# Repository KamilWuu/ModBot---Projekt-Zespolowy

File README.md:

# ModBot---Projekt-Zespolowy

1 - Założenia projektowe
Robot modułowy ModBot będzie złożony z jednostki głównej – Platformy Mobilnej wraz z pilotem zdalnego sterowania za pomocą technologii Bluetooth. Platforma ta będzie miała możliwość
doczepienia modułów określających przeznaczenie robota:

• moduł MiniSumo,

• moduł LineFollower,

• Chwytak

2 - Cel i zakres projektu
Celem projektu jest stworzenie uniwersalnej platformy robotycznej pozwalającej na edukację
w zakresie elektroniki i programowania. Osobie uczącej się przy pomocy robota będzie da-
na możliwość samodzielnego złożenia oraz zamontowania wcześniej przygotowanych modułów,
dzięki którym robot będzie mógł wykonywać określone zadanie. Planowane są trzy domyślne
konfiguracje, za pomocą których robot będzie mógł wykonać następujące zadania:

• LineFollower – podążanie wzdłuż czarnej linii kontrastowej na białym tle, która nie posiada
zakrętów ostrzejszych niż 90◦.

• RoboSumo – przesunięcie kostki o masie zbliżonej do masy robota z standardowego ringu
Minisumo i pozostanie na ringu. Ma to na celu symulacje walki z zawodów robotycznych
z kategorii MiniSumo.

• Chwytak – utrzymanie obiektu o znacznie mniejszej masie niż jego własne poprzez moduł
zdalnego sterowania.

3 - Skład zespołu:
Kamil Winnicki - Mechanika i embedded,

Oliwier Woźniak -  Elektronika,

Patryk Peroński - Oprogramowanie i embeeded,

Rafał Koziołek - Mechanika i elektronika,

Jakub Frąckowiak - Kierownik zespołu, organizacja pracy,

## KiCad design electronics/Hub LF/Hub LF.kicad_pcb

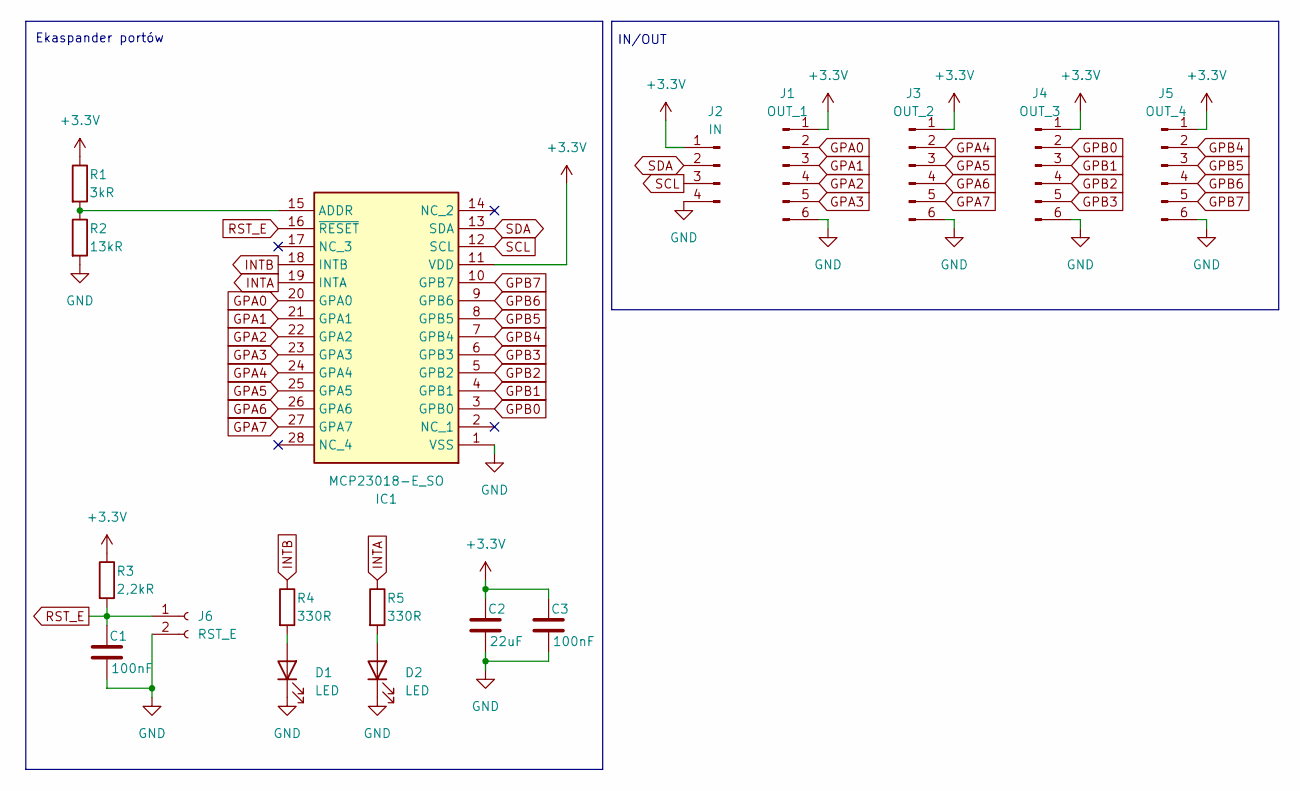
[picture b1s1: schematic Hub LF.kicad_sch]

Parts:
C1, C3: 100nF; C_0402_1005Metric_Pad0.74x0.62mm_HandSolder
C2: 22uF; C_0402_1005Metric_Pad0.74x0.62mm_HandSolder
D1, D2: LED; LED_0402_1005Metric_Pad0.77x0.64mm_HandSolder
IC1: MCP23018-E_SO; SOIC127P1030X265-28N; Manufacturer_Part_Number MCP23018-E/SO
J1: OUT_1; JST_EH_B6B-EH-A_1x06_P2.50mm_Vertical
J2: IN; JST_EH_B4B-EH-A_1x04_P2.50mm_Vertical
J3: OUT_2; JST_EH_B6B-EH-A_1x06_P2.50mm_Vertical
J4: OUT_3; JST_EH_B6B-EH-A_1x06_P2.50mm_Vertical
J5: OUT_4; JST_EH_B6B-EH-A_1x06_P2.50mm_Vertical
J6: RST_E; PinSocket_1x02_P2.54mm_Vertical
R1: 3kR; R_0402_1005Metric_Pad0.72x0.64mm_HandSolder
R2: 13kR; R_0402_1005Metric_Pad0.72x0.64mm_HandSolder
R3: 2,2kR; R_0402_1005Metric_Pad0.72x0.64mm_HandSolder
R4, R5: 330R; R_0402_1005Metric_Pad0.72x0.64mm_HandSolder

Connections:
+3.3V: C2.1, C3.1, IC1.11 (VDD), J1.1, J2.1, J3.1, J4.1, J5.1, R1.1, R3.1
GND: C1.2, C2.2, C3.2, D1.1 (K), D2.1 (K), IC1.1 (VSS), J1.6, J2.4, J3.6, J4.6, J5.6, J6.2, R2.2
GPA0: IC1.20 (GPA0), J1.2
GPA1: IC1.21 (GPA1), J1.3
GPA2: IC1.22 (GPA2), J1.4
GPA3: IC1.23 (GPA3), J1.5
GPA4: IC1.24 (GPA4), J3.2
GPA5: IC1.25 (GPA5), J3.3
GPA6: IC1.26 (GPA6), J3.4
GPA7: IC1.27 (GPA7), J3.5
GPB0: IC1.3 (GPB0), J4.2
GPB1: IC1.4 (GPB1), J4.3
GPB2: IC1.5 (GPB2), J4.4
GPB3: IC1.6 (GPB3), J4.5
GPB4: IC1.7 (GPB4), J5.2
GPB5: IC1.8 (GPB5), J5.3
GPB6: IC1.9 (GPB6), J5.4
GPB7: IC1.10 (GPB7), J5.5
INTA: IC1.19 (INTA), R5.1
INTB: IC1.18 (INTB), R4.1
unnamed: D1.2 (A), R4.2
unnamed: D2.2 (A), R5.2
unnamed: IC1.15 (ADDR), R1.2, R2.1
RST_E: C1.1, IC1.16 (~RESET), J6.1, R3.2
SCL: IC1.12 (SCL), J2.3
SDA: IC1.13 (SDA), J2.2

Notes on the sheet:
IN/OUT
Ekaspander portów

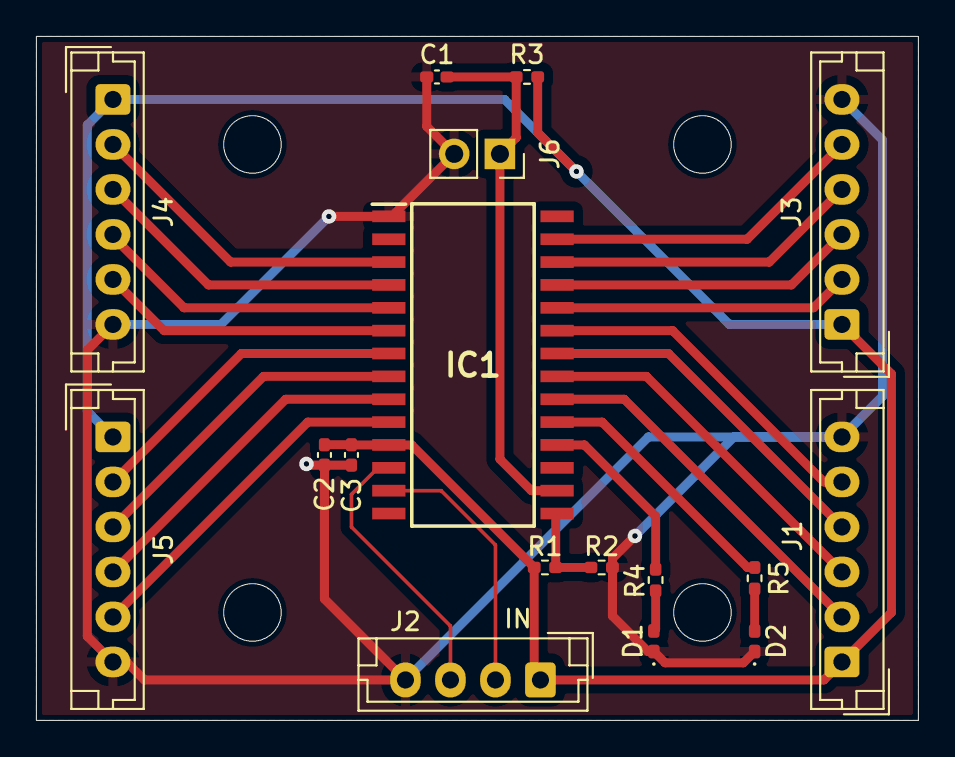
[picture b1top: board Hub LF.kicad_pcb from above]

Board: 2 copper layers, 49.0 x 38.0 mm, 17 parts (0 on the bottom side), 26 nets.

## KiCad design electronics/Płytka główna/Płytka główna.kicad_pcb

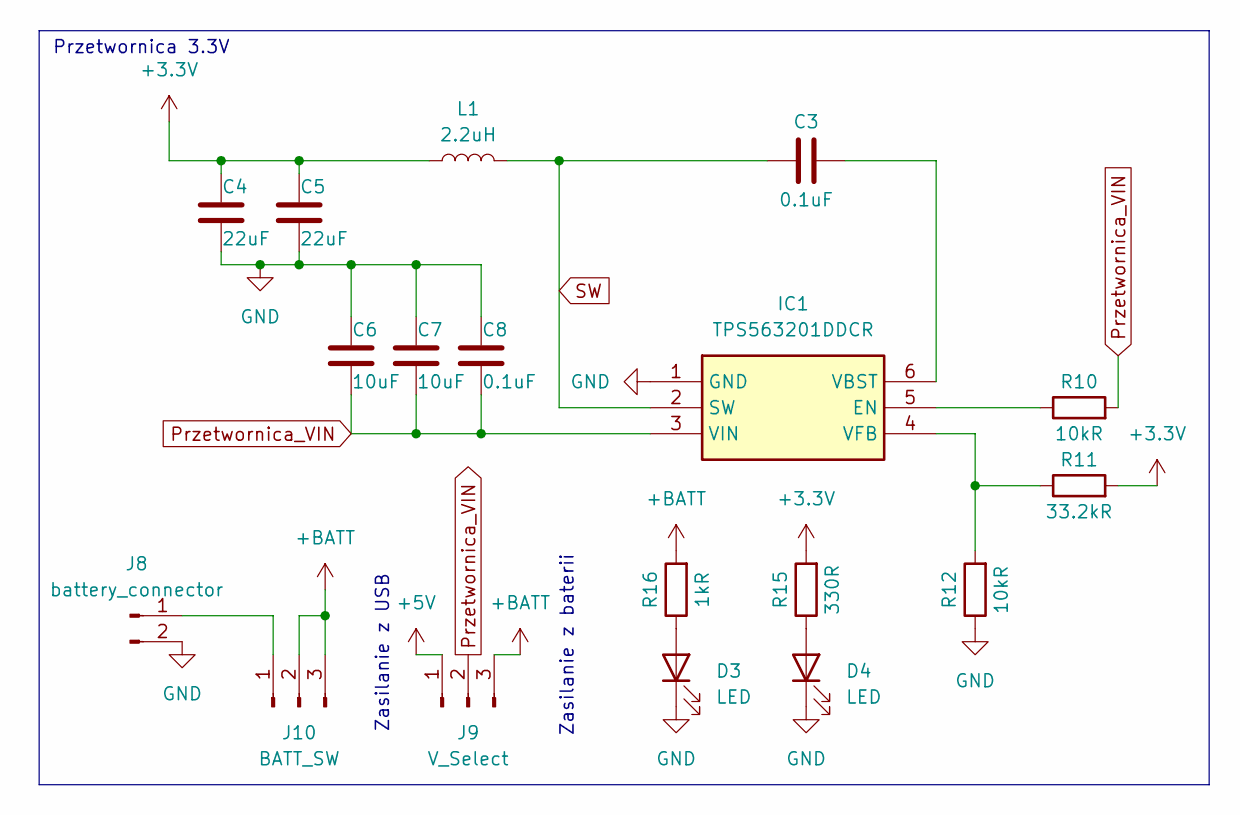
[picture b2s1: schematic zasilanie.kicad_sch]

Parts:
C3, C8: 0.1uF; C_0603_1608Metric
C4, C5: 22uF; C_0805_2012Metric
C6, C7: 10uF; C_0805_2012Metric
D3, D4: LED; LED_0402_1005Metric
IC1: TPS563201DDCR; SOT95P280X110-6N; Manufacturer_Part_Number TPS563201DDCR
J8: battery_connector; PinHeader_1x02_P2.54mm_Vertical
J9: V_Select; PinHeader_1x03_P2.54mm_Vertical
J10: BATT_SW; PinHeader_1x03_P2.54mm_Vertical
L1: 2.2uH; L_Bourns_SRP7028A_7.3x6.6mm
R10, R12: 10kR; R_0603_1608Metric
R11: 33.2kR; R_0603_1608Metric
R15: 330R; R_0603_1608Metric
R16: 1kR; R_0603_1608Metric

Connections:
+3.3V: C4.2, C5.2, L1.1, R11.2, R15.2; also elsewhere on the board
+5V: J9.1; also elsewhere on the board
+BATT: J9.3, J10.2, J10.3, R16.2; also elsewhere on the board
GND: C4.1, C5.1, C6.2, C7.2, C8.2, D3.1 (K), D4.1 (K), IC1.1 (GND), J8.2, R12.1; also elsewhere on the board
unnamed: D3.2 (A), R16.1
unnamed: D4.2 (A), R15.1
unnamed: IC1.5 (EN), R10.1
unnamed: C3.2, IC1.6 (VBST)
unnamed: IC1.4 (VFB), R11.1, R12.2
unnamed: J8.1, J10.1
Przetwornica_VIN: C6.1, C7.1, C8.1, IC1.3 (VIN), J9.2, R10.2
SW: C3.1, IC1.2 (SW), L1.2

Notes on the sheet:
Zasilanie z baterii
Przetwornica 3.3V
Zasilanie z USB

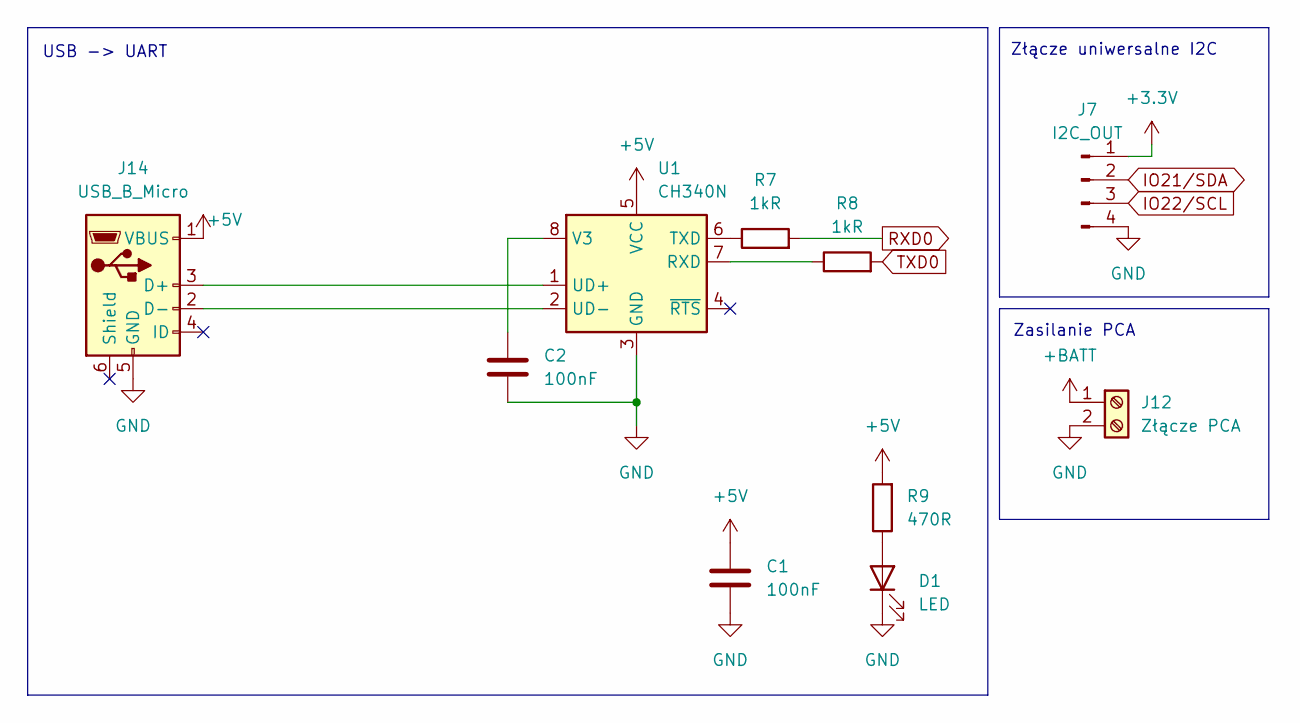
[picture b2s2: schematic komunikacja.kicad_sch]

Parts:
C1, C2: 100nF; C_0402_1005Metric_Pad0.74x0.62mm_HandSolder
D1: LED; LED_0402_1005Metric
J7: I2C_OUT; JST_EH_B4B-EH-A_1x04_P2.50mm_Vertical
J12: Złącze PCA; ARK 01x02 5mm
J14: USB_B_Micro; USB_Micro-B_Amphenol_10118194_Horizontal
R7, R8: 1kR; R_0402_1005Metric_Pad0.72x0.64mm_HandSolder
R9: 470R; R_0402_1005Metric_Pad0.72x0.64mm_HandSolder
U1: CH340N; SOP-8_3.9x4.9mm_P1.27mm

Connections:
+3.3V: J7.1; also elsewhere on the board
+5V: C1.1, J14.1 (VBUS), R9.2, U1.5 (VCC); also elsewhere on the board
+BATT: J12.1; also elsewhere on the board
GND: C1.2, C2.2, D1.1 (K), J7.4, J12.2, J14.5 (GND), U1.3 (GND); also elsewhere on the board
IO21/SDA: J7.2; also elsewhere on the board
IO22/SCL: J7.3; also elsewhere on the board
unnamed: D1.2 (A), R9.1
unnamed: J14.3 (D+), U1.1 (UD+)
unnamed: J14.2 (D-), U1.2 (UD-)
unnamed: R8.1, U1.7 (RXD)
unnamed: R7.1, U1.6 (TXD)
unnamed: C2.1, U1.8 (V3)
RXD0: R7.2; also elsewhere on the board
TXD0: R8.2; also elsewhere on the board

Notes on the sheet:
Zasilanie PCA
USB -> UART
Złącze uniwersalne I2C

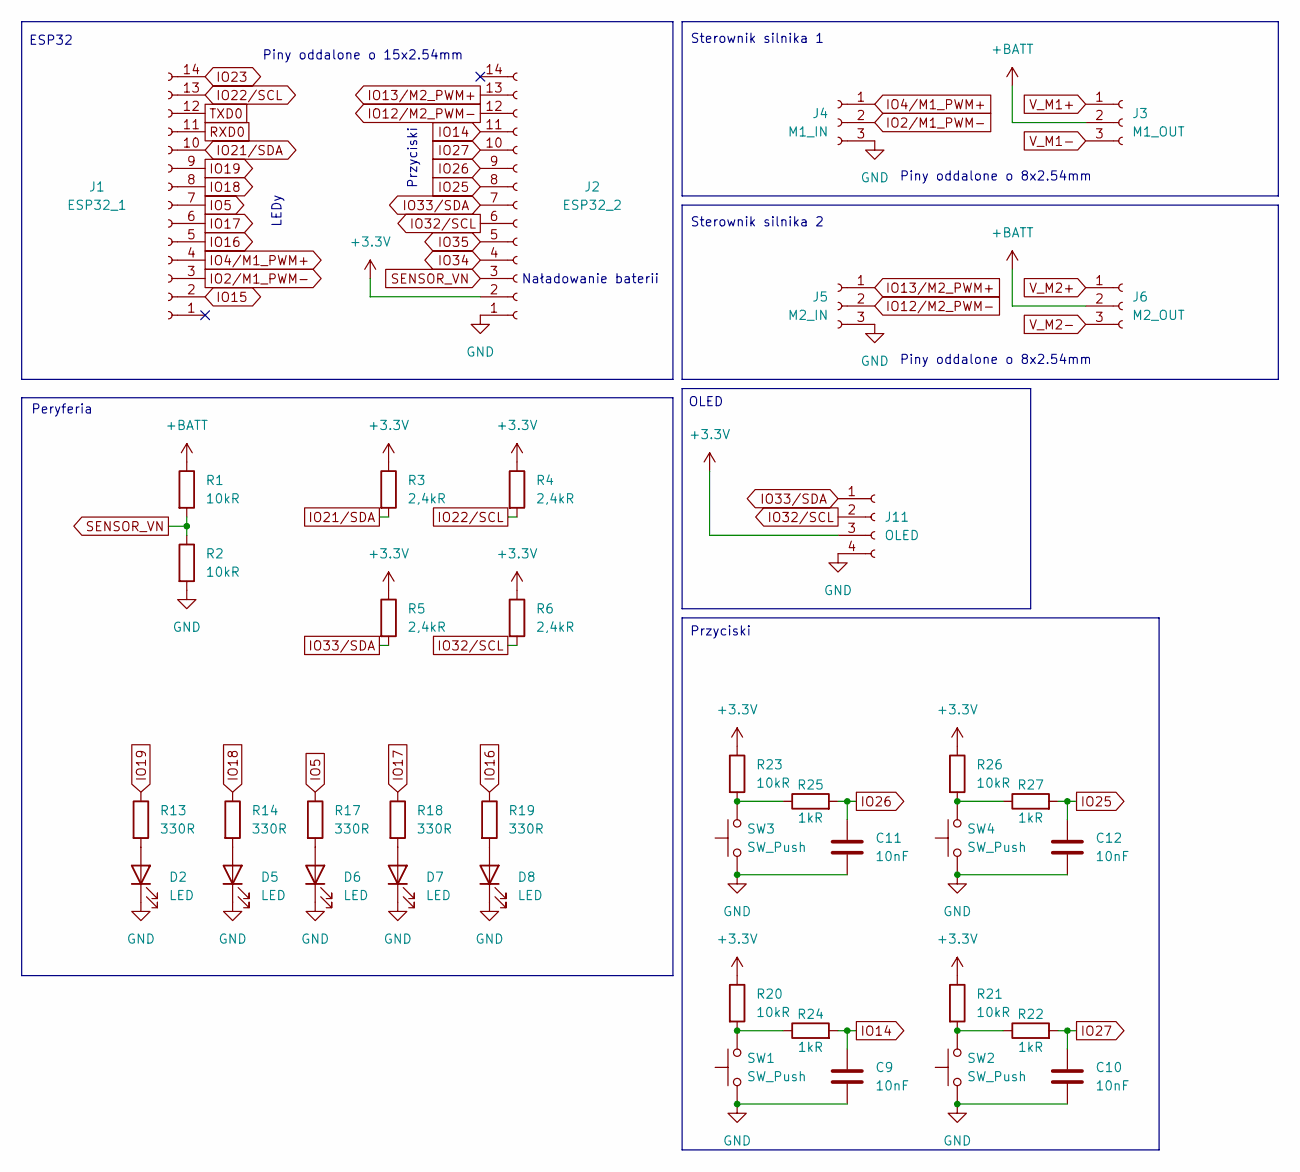
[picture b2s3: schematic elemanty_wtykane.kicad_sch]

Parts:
C9, C10, C11, C12: 10nF; C_0402_1005Metric_Pad0.74x0.62mm_HandSolder
D2, D5, D6, D7, D8: LED; LED_0402_1005Metric
J1: ESP32_1; PinSocket_1x14_P2.54mm_Vertical
J2: ESP32_2; PinSocket_1x14_P2.54mm_Vertical
J3: M1_OUT; PinSocket_1x03_P2.54mm_Vertical
J4: M1_IN; PinSocket_1x03_P2.54mm_Vertical
J5: M2_IN; PinSocket_1x03_P2.54mm_Vertical
J6: M2_OUT; PinSocket_1x03_P2.54mm_Vertical
J11: OLED; PinSocket_1x04_P2.54mm_Vertical
R1, R2, R20, R21, R23, R26: 10kR; R_0402_1005Metric_Pad0.72x0.64mm_HandSolder
R3, R4, R5, R6: 2,4kR; R_0402_1005Metric_Pad0.72x0.64mm_HandSolder
R13, R14, R17, R18, R19: 330R; R_0402_1005Metric_Pad0.72x0.64mm_HandSolder
R22, R24, R25, R27: 1kR; R_0402_1005Metric_Pad0.72x0.64mm_HandSolder
SW1, SW2, SW3, SW4: SW_Push; SW_PUSH_6mm_H5mm

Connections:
+3.3V: J2.2, J11.3, R3.1, R4.1, R5.1, R6.1, R20.1, R21.1, R23.1, R26.1; also elsewhere on the board
+BATT: J3.2, J6.2, R1.1; also elsewhere on the board
GND: C9.2, C10.2, C11.2, C12.2, D2.1 (K), D5.1 (K), D6.1 (K), D7.1 (K), D8.1 (K), J2.1, J4.3, J5.3, J11.4, R2.2, SW1.1, SW2.1, SW3.1, SW4.1; also elsewhere on the board
IO2/M1_PWM-: J1.3, J4.2
IO4/M1_PWM+: J1.4, J4.1
IO5: J1.7, R17.1
IO12/M2_PWM-: J2.12, J5.2
IO13/M2_PWM+: J2.13, J5.1
IO14: C9.1, J2.11, R24.2
IO15: J1.2
IO16: J1.5, R19.1
IO17: J1.6, R18.1
IO18: J1.8, R14.1
IO19: J1.9, R13.1
IO21/SDA: J1.10, R3.2; also elsewhere on the board
IO22/SCL: J1.13, R4.2; also elsewhere on the board
IO23: J1.14
IO25: C12.1, J2.8, R27.2
IO26: C11.1, J2.9, R25.2
IO27: C10.1, J2.10, R22.2
IO32/SCL: J2.6, J11.2, R6.2
IO33/SDA: J2.7, J11.1, R5.2
IO34: J2.4
IO35: J2.5
unnamed: D2.2 (A), R13.2
unnamed: D5.2 (A), R14.2
unnamed: D6.2 (A), R17.2
unnamed: D7.2 (A), R18.2
unnamed: D8.2 (A), R19.2
unnamed: R20.2, R24.1, SW1.2
unnamed: R21.2, R22.1, SW2.2
unnamed: R23.2, R25.1, SW3.2
unnamed: R26.2, R27.1, SW4.2
RXD0: J1.11; also elsewhere on the board
SENSOR_VN: J2.3, R1.2, R2.1
TXD0: J1.12; also elsewhere on the board
V_M1+: J3.1
V_M1-: J3.3
V_M2+: J6.1
V_M2-: J6.3

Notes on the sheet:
OLED
Peryferia
Przyciski
Piny oddalone o 8x2.54mm
Sterownik silnika 1
Naładowanie baterii
LEDy
ESP32
Sterownik silnika 2
Piny oddalone o 15x2.54mm
Przyciski

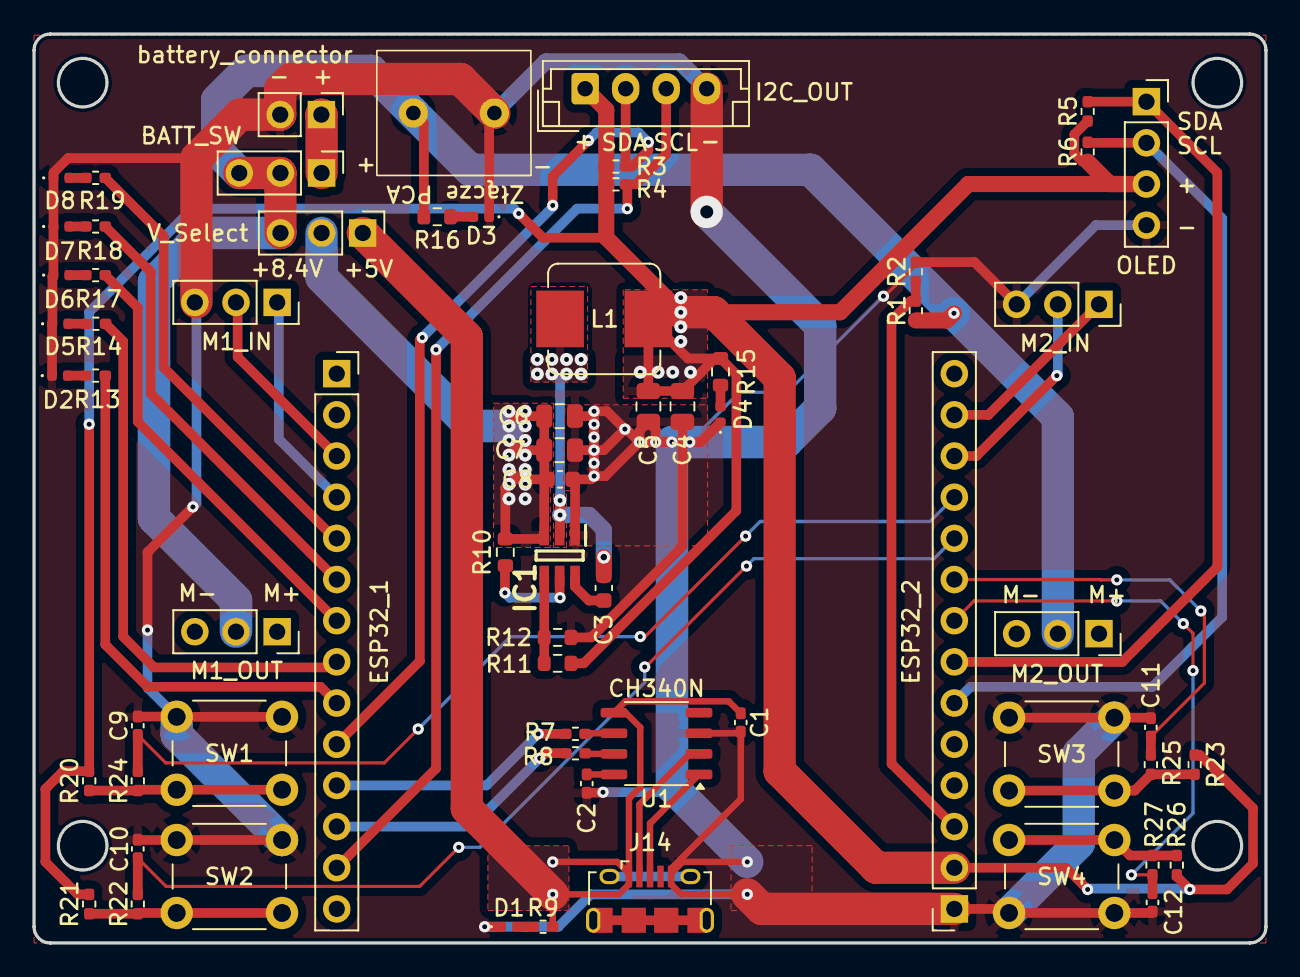
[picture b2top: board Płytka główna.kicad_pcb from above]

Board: 2 copper layers, 76.0 x 56.1 mm, 67 parts (0 on the bottom side), 47 nets.

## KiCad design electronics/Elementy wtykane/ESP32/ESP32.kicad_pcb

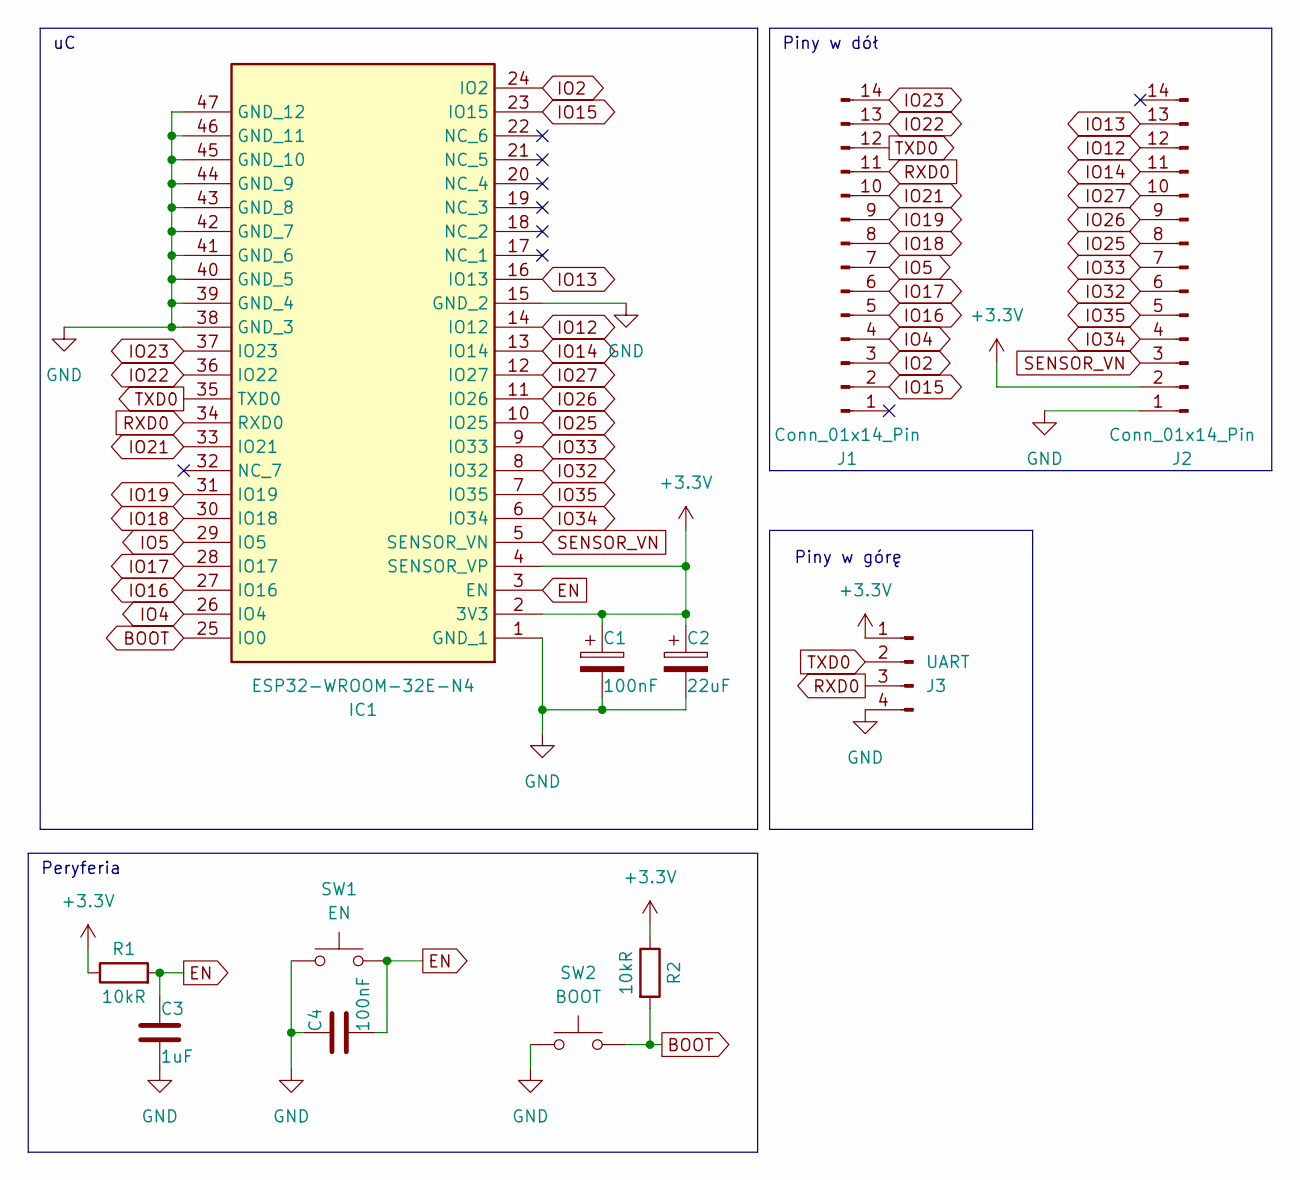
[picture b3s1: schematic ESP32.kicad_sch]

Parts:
C1, C4: 100nF; C_0402_1005Metric_Pad0.74x0.62mm_HandSolder
C2: 22uF; C_0402_1005Metric_Pad0.74x0.62mm_HandSolder
C3: 1uF; C_0402_1005Metric_Pad0.74x0.62mm_HandSolder
IC1: ESP32-WROOM-32E-N4; ESP32WROOM32EN4; Manufacturer_Part_Number ESP32-WROOM-32E-N4
J1, J2: Conn_01x14_Pin; PinHeader_1x14_P2.54mm_Vertical
J3: UART; PinHeader_1x04_P2.54mm_Vertical
R1, R2: 10kR; R_0402_1005Metric_Pad0.72x0.64mm_HandSolder
SW1: EN; SW_Push_1P1T_XKB_TS-1187A
SW2: BOOT; SW_Push_1P1T_XKB_TS-1187A

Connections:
+3.3V: C1.1, C2.1, IC1.2 (3V3), IC1.4 (SENSOR_VP), J2.2, J3.1, R1.1, R2.1
BOOT: IC1.25 (IO0), R2.2, SW2.2
EN: C3.1, C4.2, IC1.3 (EN), R1.2, SW1.2
GND: C1.2, C2.2, C3.2, C4.1, IC1.1 (GND_1), IC1.15 (GND_2), IC1.38 (GND_3), IC1.39 (GND_4), IC1.40 (GND_5), IC1.41 (GND_6), IC1.42 (GND_7), IC1.43 (GND_8), IC1.44 (GND_9), IC1.45 (GND_10), IC1.46 (GND_11), IC1.47 (GND_12), J2.1, J3.4, SW1.1, SW2.1
IO2: IC1.24 (IO2), J1.3
IO4: IC1.26 (IO4), J1.4
IO5: IC1.29 (IO5), J1.7
IO12: IC1.14 (IO12), J2.12
IO13: IC1.16 (IO13), J2.13
IO14: IC1.13 (IO14), J2.11
IO15: IC1.23 (IO15), J1.2
IO16: IC1.27 (IO16), J1.5
IO17: IC1.28 (IO17), J1.6
IO18: IC1.30 (IO18), J1.8
IO19: IC1.31 (IO19), J1.9
IO21: IC1.33 (IO21), J1.10
IO22: IC1.36 (IO22), J1.13
IO23: IC1.37 (IO23), J1.14
IO25: IC1.10 (IO25), J2.8
IO26: IC1.11 (IO26), J2.9
IO27: IC1.12 (IO27), J2.10
IO32: IC1.8 (IO32), J2.6
IO33: IC1.9 (IO33), J2.7
IO34: IC1.6 (IO34), J2.4
IO35: IC1.7 (IO35), J2.5
RXD0: IC1.34 (RXD0), J1.11, J3.3
SENSOR_VN: IC1.5 (SENSOR_VN), J2.3
TXD0: IC1.35 (TXD0), J1.12, J3.2

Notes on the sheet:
Piny w górę
Piny w dół
Peryferia

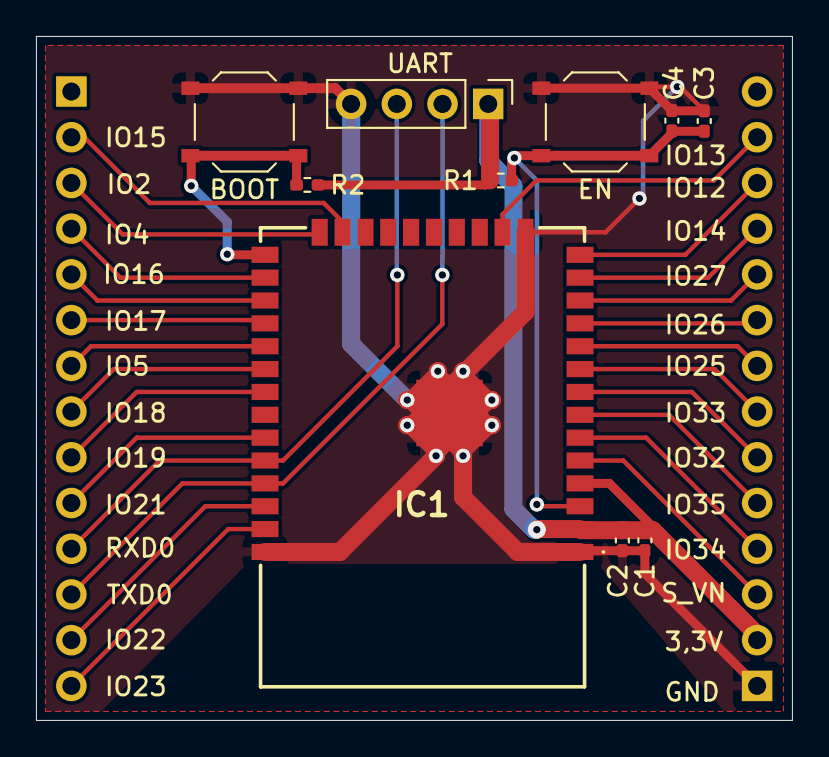
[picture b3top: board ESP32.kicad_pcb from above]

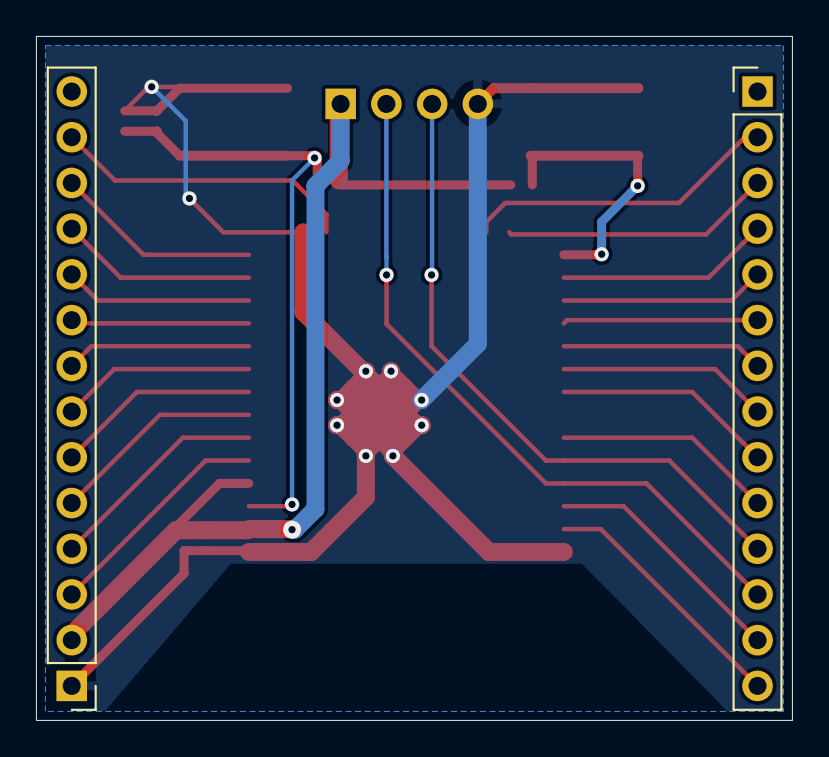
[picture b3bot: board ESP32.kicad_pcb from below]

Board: 2 copper layers, 42.0 x 38.0 mm, 12 parts (2 on the bottom side), 28 nets.

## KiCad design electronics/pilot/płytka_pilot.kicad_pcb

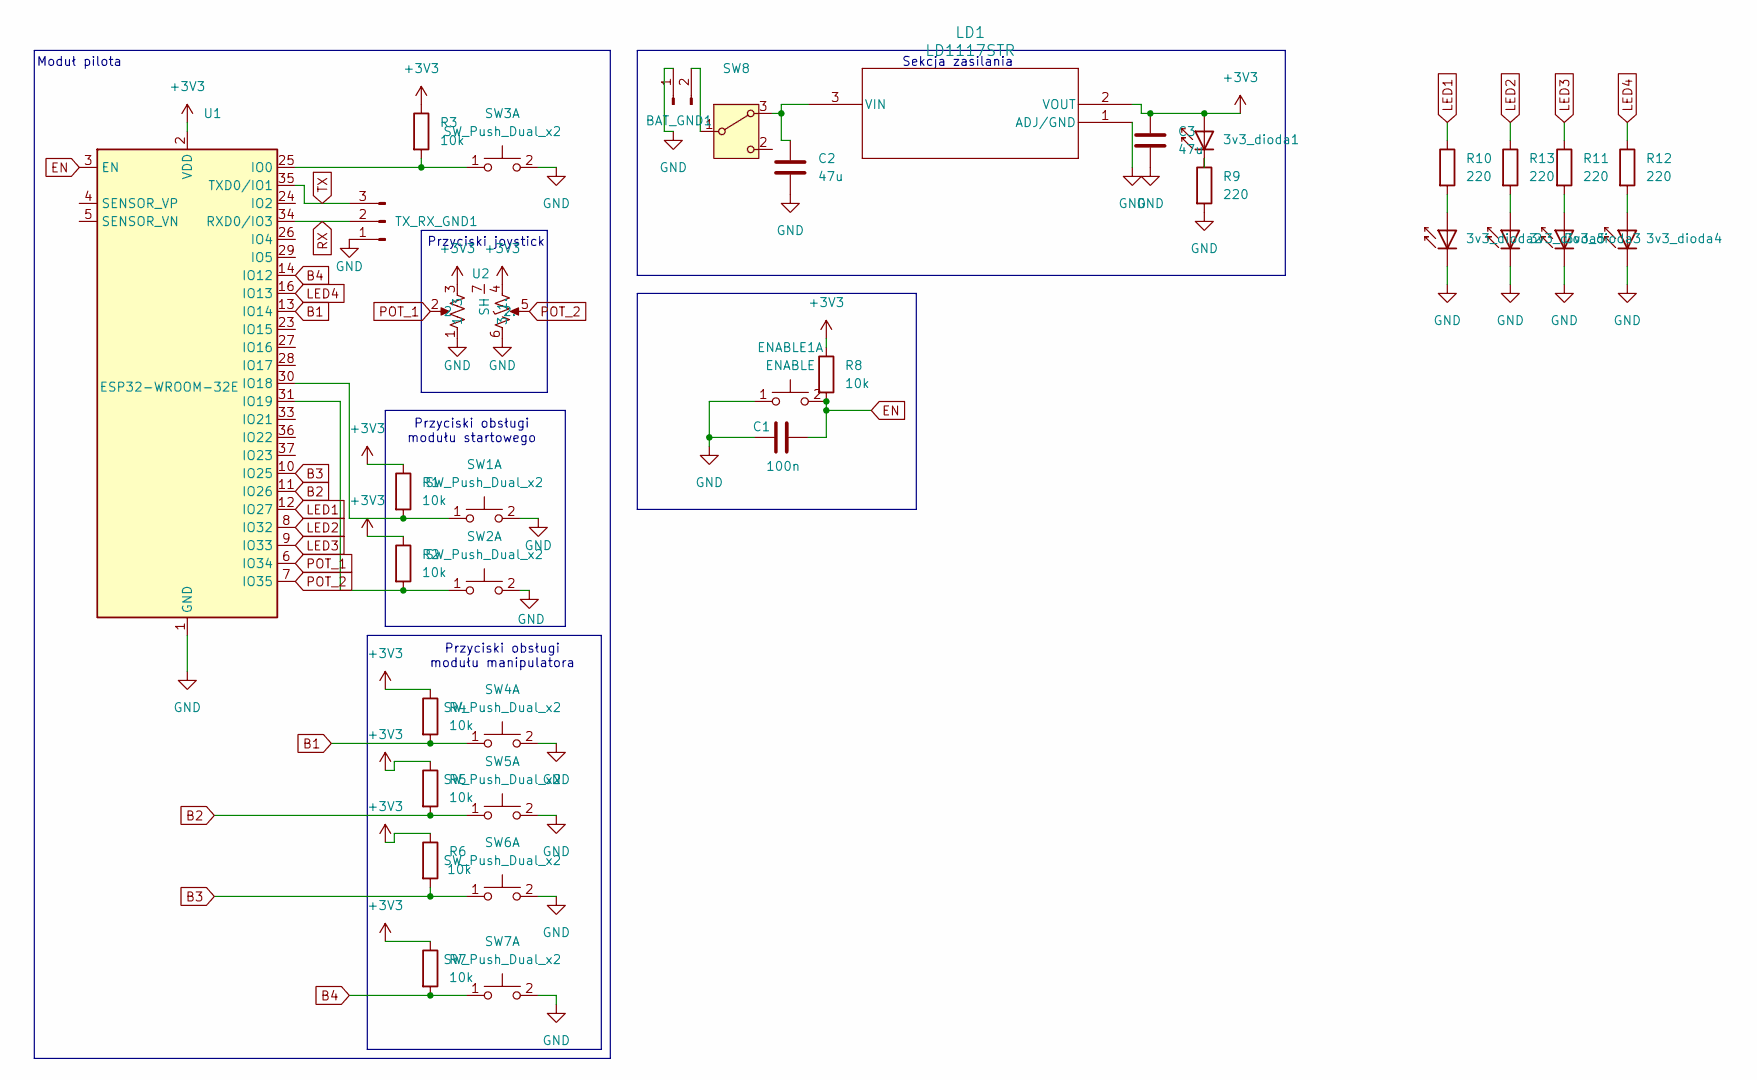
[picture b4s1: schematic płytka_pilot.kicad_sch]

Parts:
3v3_dioda1, 3v3_dioda2, 3v3_dioda3, 3v3_dioda4, 3v3_dioda5: IR204A; LED_D3.0mm_IRBlack
BAT_GND1: Conn_01x02_Pin; PinHeader_1x02_P2.54mm_Vertical
C1: 100n; C_0603_1608Metric
C2, C3: 47u; CP_EIA-3528-21_Kemet-B_Pad1.50x2.35mm_HandSolder
ENABLE1: ENABLE; SW_Push_1P1T_XKB_TS-1187A
LD1: LD1117STR; SOT-223
R1, R2, R3, R4, R5, R6, R7, R8: 10k; R_0603_1608Metric
R9, R10, R11, R12, R13: 220; R_0603_1608Metric
SW1, SW2, SW4, SW5, SW6, SW7: SW_Push_Dual_x2; SW_PUSH_6mm
SW3: SW_Push_Dual_x2; SW_Push_1P1T_XKB_TS-1187A
SW8: SW_Wuerth_450301014042; SW_Slide-03_Wuerth-WS-SLTV_10x2.5x6.4_P2.54mm
TX_RX_GND1: Conn_01x03_Pin; PinSocket_1x03_P2.54mm_Vertical
U1: ESP32-WROOM-32E; ESP32-WROOM-32D
U2: 3D161

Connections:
+3V3: 3v3_dioda1.2 (A), C3.1, LD1.2 (VOUT), R1.1, R2.1, R3.1, R4.1, R5.1, R6.1, R7.1, R8.1, U1.2 (VDD), U2.3, U2.4 (1.)
B1: R4.2, SW4.1 (C), U1.13 (IO14)
B2: R5.2, SW5.1 (C), U1.11 (IO26)
B3: R6.2, SW6.1 (C), U1.10 (IO25)
B4: R7.2, SW7.1 (C), U1.14 (IO12)
EN: C1.2, ENABLE1.2 (D), R8.2, U1.3 (EN); also elsewhere on the board
GND: 3v3_dioda2.1 (K), 3v3_dioda3.1 (K), 3v3_dioda4.1 (K), 3v3_dioda5.1 (K), BAT_GND1.1, C1.1, C2.2, C3.2, ENABLE1.1 (C), LD1.1 (ADJ/GND), R9.2, SW1.2 (D), SW2.2 (D), SW3.2 (D), SW4.2 (D), SW5.2 (D), SW6.2 (D), SW7.2 (D), TX_RX_GND1.1, U1.1 (GND), U1.15 (GND), U1.38 (GND), U1.39 (GND), U2.1, U2.6 (3.); also elsewhere on the board
LED1: R10.1, U1.12 (IO27)
LED2: R13.1, U1.8 (IO32)
LED3: R11.1, U1.9 (IO33)
LED4: R12.1, U1.16 (IO13)
unnamed: 3v3_dioda1.1 (K), R9.1
unnamed: 3v3_dioda2.2 (A), R10.2
unnamed: 3v3_dioda3.2 (A), R11.2
unnamed: 3v3_dioda4.2 (A), R12.2
unnamed: 3v3_dioda5.2 (A), R13.2
unnamed: BAT_GND1.2, SW8.1 (B)
unnamed: C2.1, LD1.3 (VIN), SW8.3 (A)
unnamed: R1.2, SW1.1 (C), U1.30 (IO18)
unnamed: R2.2, SW2.1 (C), U1.31 (IO19)
unnamed 20: R3.2, SW3.1 (C), U1.25 (IO0); also elsewhere on the board
POT_1: U1.6 (IO34), U2.2
POT_2: U1.7 (IO35), U2.5 (2.)
RX: TX_RX_GND1.2, U1.34 (RXD0/IO3)
TX: TX_RX_GND1.3, U1.35 (TXD0/IO1)

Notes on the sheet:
Moduł pilota
Przyciski joystick
Przyciski obsługi modułu startowego
Sekcja zasilania
Przyciski obsługi modułu manipulatora

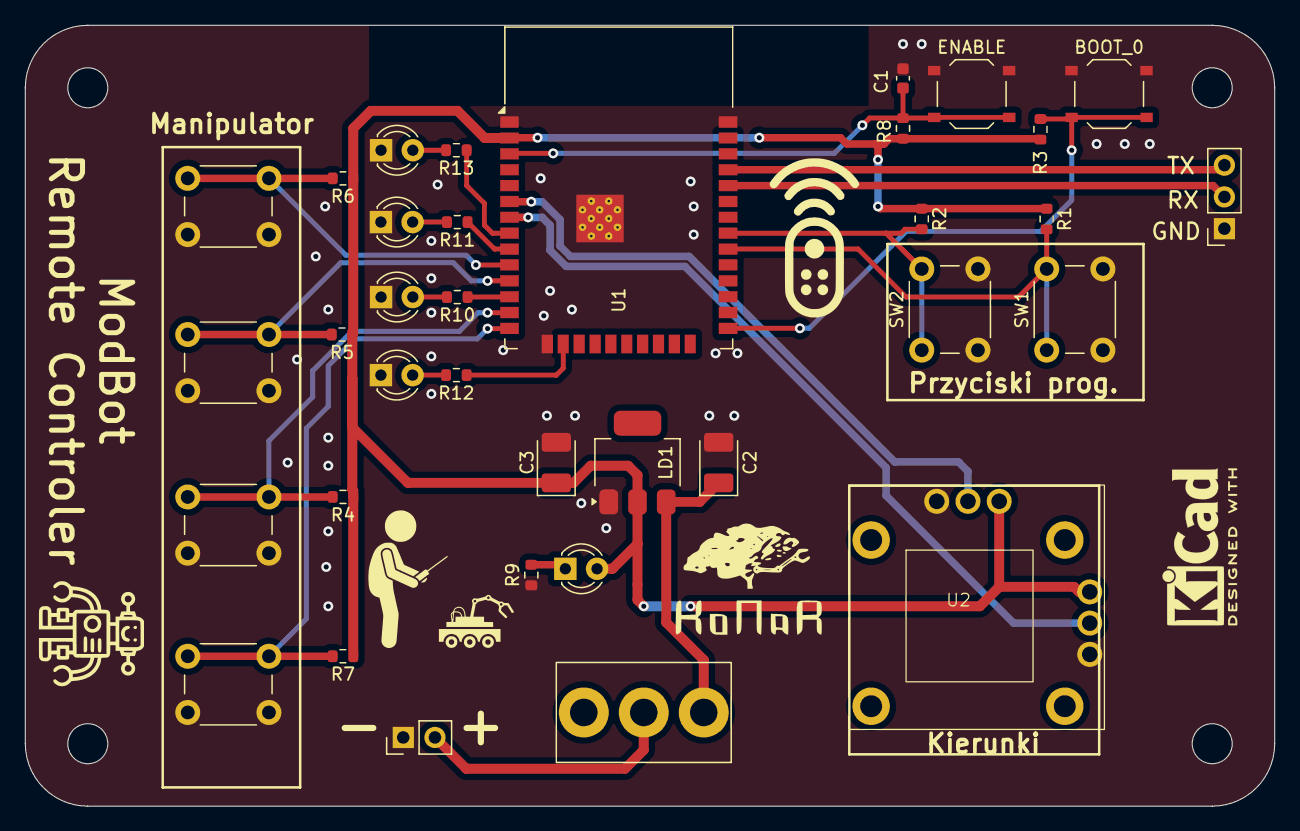
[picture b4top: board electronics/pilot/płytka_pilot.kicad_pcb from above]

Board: 2 copper layers, 100.0 x 62.5 mm, 35 parts (0 on the bottom side), 25 nets.

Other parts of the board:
BOOT_0: SW_Push_Dual_x2; SW_Push_1P1T_XKB_TS-1187A
ENABLE: ENABLE; SW_Push_1P1T_XKB_TS-1187A

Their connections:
EN: ENABLE.2 (D); also elsewhere on the board
GND: BOOT_0.2 (D), ENABLE.1 (C); also elsewhere on the board
unnamed 20: BOOT_0.1 (C); also elsewhere on the board

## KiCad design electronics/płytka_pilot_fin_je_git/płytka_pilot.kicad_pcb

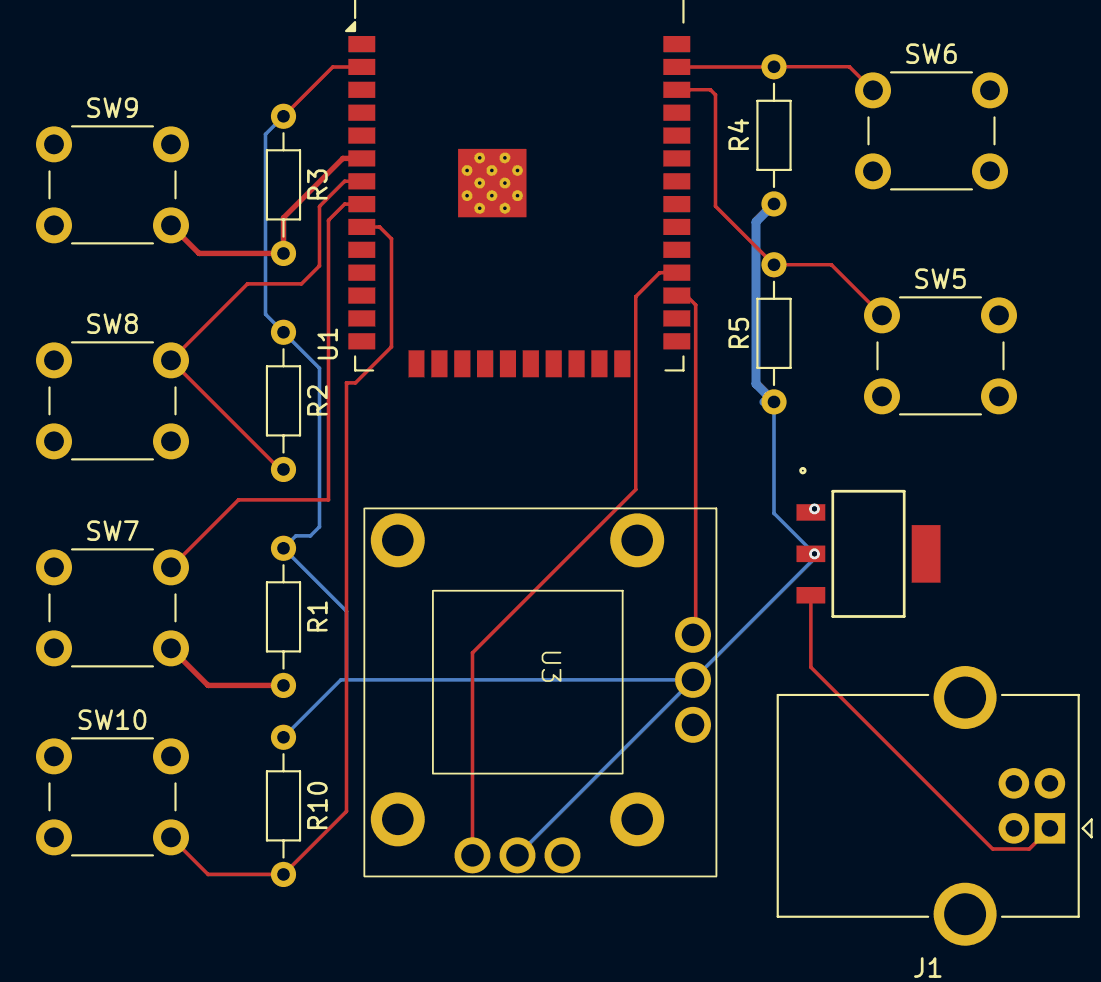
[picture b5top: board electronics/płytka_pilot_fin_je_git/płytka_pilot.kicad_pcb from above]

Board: 2 copper layers, 16 parts (0 on the bottom side), 11 nets.

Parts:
CR1: LD1117STR; SOT-223_STM
J1: USB_B; USB_B_OST_USB-B1HSxx_Horizontal
R1, R2, R3, R4, R5, R10: 10k; R_Axial_DIN0204_L3.6mm_D1.6mm_P7.62mm_Horizontal
SW5: START_start; SW_PUSH_6mm_H5mm
SW6: START_stop; SW_PUSH_6mm_H5mm
SW7: ramie_1; SW_PUSH_6mm_H5mm
SW8: ramie_2; SW_PUSH_6mm_H5mm
SW9: ramie_3; SW_PUSH_6mm_H5mm
SW10: ramie_4; SW_PUSH_6mm_H5mm
U1: ESP32-WROOM-32E; ESP32-WROOM-32D
U3: 3D161

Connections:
+3V3: CR1.2 (VOUT), R1.1, R2.1, R3.1, R4.1, R5.1, R10.1, U1.2 (VDD), U3.2, U3.5 (2.)
GND: CR1.1 (ADJ/GND), J1.4 (GND), J1.5 (Shield), U1.1 (GND), U1.15 (GND), U1.38 (GND), U1.39 (GND)
unnamed: CR1.3 (VIN), J1.1 (VBUS)
unnamed: U1.27 (IO16), U3.1
unnamed: U1.28 (IO17), U3.6 (3.)
unnamed: R5.2, SW5.1 (A), SW5.2 (A), U1.36 (IO22)
unnamed: R4.2, SW6.1 (A), SW6.2 (A), U1.37 (IO23)
unnamed: R1.2, SW7.1 (A), SW7.2 (A), U1.8 (IO32)
unnamed: R10.2, SW10.1 (A), SW10.2 (A), U1.9 (IO33)
unnamed: R3.2, SW9.1 (A), SW9.2 (A), U1.6 (IO34)
unnamed: R2.2, SW8.1 (A), SW8.2 (A), U1.7 (IO35)

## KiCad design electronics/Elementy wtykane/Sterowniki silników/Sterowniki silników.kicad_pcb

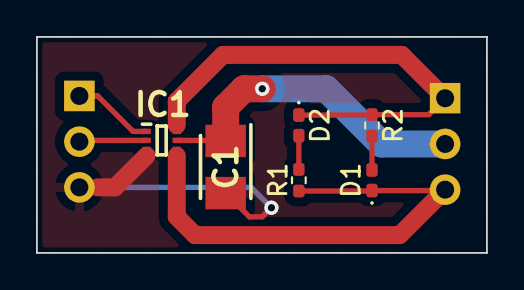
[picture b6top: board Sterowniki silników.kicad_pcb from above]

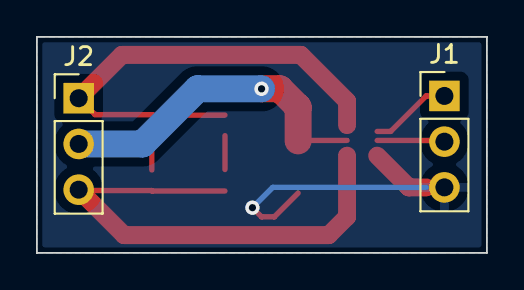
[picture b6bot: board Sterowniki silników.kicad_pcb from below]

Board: 2 copper layers, 25.0 x 12.0 mm, 8 parts (2 on the bottom side), 8 nets.

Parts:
C1: C_Polarized; CAPPM3528X210N
D1, D2: LED; D_0402_1005Metric_Pad0.77x0.64mm_HandSolder
IC1: DRV8210DRLR; SOTFL50P160X60-6N
J1, J2: Conn_01x03_Pin; PinHeader_1x03_P2.54mm_Vertical
R1, R2: 500R; R_0402_1005Metric_Pad0.72x0.64mm_HandSolder

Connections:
GND: C1.2, IC1.3 (GND), J1.3
unnamed: D1.2 (A), R2.2
unnamed: D2.2 (A), R1.2
PWM_DRV1: IC1.1 (IN1), J1.1
PWM_DRV2: IC1.2 (IN2), J1.2
VDD: C1.1, IC1.5 (VM), J2.2
V_M1: D2.1 (K), IC1.6 (OUT1), J2.1, R2.1
V_M2: D1.1 (K), IC1.4 (OUT2), J2.3, R1.1
